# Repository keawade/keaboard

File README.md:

# keaboard

A split ergo 4x6 keyboard designed by Keith Wade.

Designed for use with the [nice!nano][nicenanoDocs] USB-C Bluetooth Pro Micro replacement
but also works with any Pro Micro compatible controllers like the Elite-C.

Inspired by the [ErgoTravel][ergotravel] keyboard designed by @jpconstantineau.

## Primary Features

- Split
- Columnular stagger
- Wireless option
- Hot swap MX switches
- Reversible PCB

## Revision 1

### PCB

### PCB Case

## Parts List

| Qty                   | Part                                                                                      |
| --------------------- | ----------------------------------------------------------------------------------------- |
| 2                     | Pro Micro footprint compatible microcontroller (Recommend Elite-C if not using nice!nano) |
| 50                    | MX compatible keyboard switches                                                           |  |
| 2 sets of 12 pins     | Mill-Max low profile sockets                                                              |
| 24 (get extra though) | Mill-Max low profile pins                                                                 |
| 50                    | Kailh MX hot swap sockets                                                                 |
| 50                    | MX compatible switches                                                                    |
| 50                    | [1N4148W SMD diodes][diodes]                                                              |
| 2                     | PJ-320A TRRS female jack  (not required if wireless with nice!nano)                       |
| 2                     | [EVQ-9P701P tactile switch](resetSwitch)                                                  |
| 24                    | M2 x 4 mm screws                                                                          |
| 12                    | M2 x 7mm stand offs                                                                       |

### Parts for Wireless Option

| Qty | Part                                                             |
| --- | ---------------------------------------------------------------- |
| 2   | [nice!nano][nicenanoStore]                                       |
| 2   | [CUS-12TB][slideSwitch] for power switch                         |
| 2   | 3.7v rechargeable battery                                        |
| 2   | [3-pin socket][batterySocket] (Can solder directly if preferred) |
| 2   | 2-pin plug                                                       |

## Firmware

- [QMK Firmware][keaboardQmk]
- [ZMK Firmware][keaboardZmk]

## Potential Future Revisions

- Choc hot swap
- RGB underglow
- LED backlight
- RGB backlight
- Design case for either 3D printing or CNC

[nicenanoDocs]: https://docs.nicekeyboards.com/#/nice!nano/
[nicenanoStore]: https://splitkb.com/collections/keyboard-parts/products/nice-nano-rev1-0
[ergotravel]: https://github.com/jpconstantineau/ErgoTravel
[batterySocket]: https://www.digikey.com/product-detail/en/DF3A-3P-2DS/H3894-ND/560460
[diodes]: https://www.digikey.com/product-detail/en/1N4148W-G+RHG/1N4148W-GRHGCT-ND/7644279
[slideSwitch]: https://www.digikey.com/product-detail/en/nidec-copal-electronics/CUS-12TB/563-1102-1-ND/1124231
[resetSwitch]: https://www.digikey.com/product-detail/en/panasonic-electronic-components/EVQ-9P701P/P19095CT-ND/5872974
[keaboardQmk]: https://github.com/keawade/qmk_firmware/tree/keaboard
[keaboardZmk]: https://github.com/keawade/keaboard-zmk-config

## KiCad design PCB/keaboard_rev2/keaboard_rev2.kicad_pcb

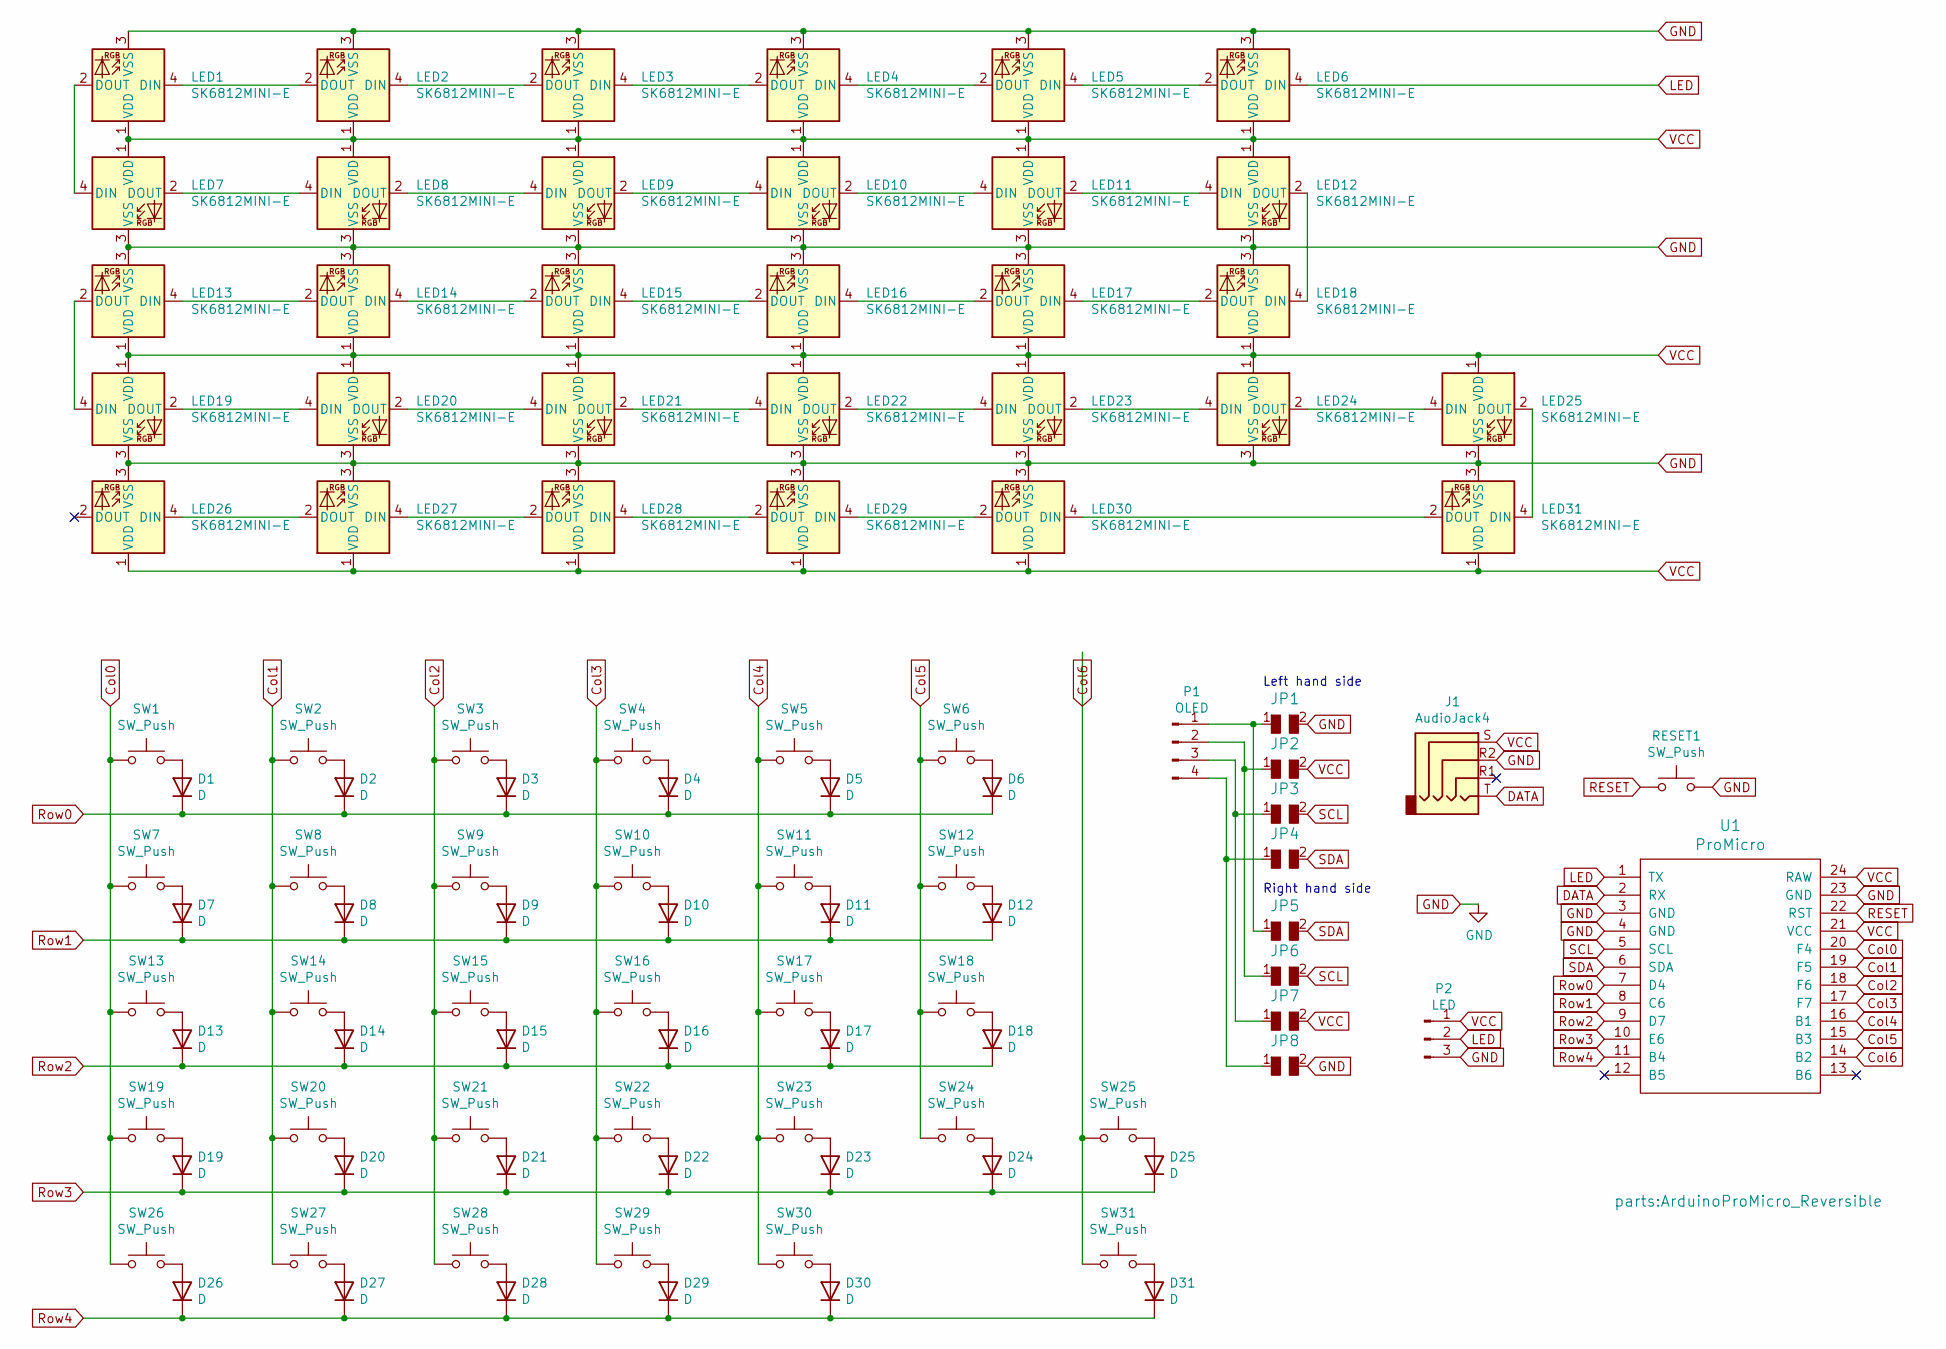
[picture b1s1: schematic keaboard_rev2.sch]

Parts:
D1, D2, D3, D4, D5, D6, D7, D8, D9, D10, D11, D12, D13, D14, D15, D16, D17, D18, D19, D20, D21, D22, D23, D24, D25, D26, D27, D28, D29, D30, D31: D; Diode-dual
J1: AudioJack4; TRRS-PJ-320A_reversible
JP1, JP8: GND; Jumper
JP2, JP7: VCC; Jumper
JP3, JP6: SCL; Jumper
JP4, JP5: SDA; Jumper
LED1, LED2, LED3, LED4, LED5, LED6, LED7, LED8, LED9, LED10, LED11, LED12, LED13, LED14, LED15, LED16, LED17, LED18, LED19, LED20, LED21, LED22, LED23, LED24, LED25, LED26, LED27, LED28, LED29, LED30, LED31: SK6812MINI-E; SK6812MINI-E_reversible
P1: OLED; OLED_v2
P2: LED; StripLED_reversible
RESET1: SW_Push; SW_EVQ-9P701P_reversible
SW1, SW2, SW3, SW4, SW5, SW6, SW7, SW8, SW9, SW10, SW11, SW12, SW13, SW14, SW15, SW16, SW17, SW18, SW19, SW20, SW21, SW22, SW23, SW24, SW25, SW26, SW27, SW28, SW29, SW30, SW31: SW_Push; Kailh_socket_PG1350_reversible
U1: ProMicro; ArduinoProMicro_Reversible

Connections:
Col0: SW1.1, SW7.1, SW13.1, SW19.1, SW26.1, U1.20 (F4)
Col1: SW2.1, SW8.1, SW14.1, SW20.1, SW27.1, U1.19 (F5)
Col2: SW3.1, SW9.1, SW15.1, SW21.1, SW28.1, U1.18 (F6)
Col3: SW4.1, SW10.1, SW16.1, SW22.1, SW29.1, U1.17 (F7)
Col4: SW5.1, SW11.1, SW17.1, SW23.1, SW30.1, U1.16 (B1)
Col5: SW6.1, SW12.1, SW18.1, SW24.1, U1.15 (B3)
Col6: SW25.1, SW31.1, U1.14 (B2)
DATA: J1.T, U1.2 (RX)
GND: J1.R2, JP1.2, JP8.2, LED1.3 (VSS), LED2.3 (VSS), LED3.3 (VSS), LED4.3 (VSS), LED5.3 (VSS), LED6.3 (VSS), LED7.3 (VSS), LED8.3 (VSS), LED9.3 (VSS), LED10.3 (VSS), LED11.3 (VSS), LED12.3 (VSS), LED13.3 (VSS), LED14.3 (VSS), LED15.3 (VSS), LED16.3 (VSS), LED17.3 (VSS), LED18.3 (VSS), LED19.3 (VSS), LED20.3 (VSS), LED21.3 (VSS), LED22.3 (VSS), LED23.3 (VSS), LED24.3 (VSS), LED25.3 (VSS), LED26.3 (VSS), LED27.3 (VSS), LED28.3 (VSS), LED29.3 (VSS), LED30.3 (VSS), LED31.3 (VSS), P2.3, RESET1.2, U1.3 (GND), U1.4 (GND), U1.23 (GND)
LED: LED6.4 (DIN), P2.2, U1.1 (TX)
unnamed: D1.2 (A), SW1.2
unnamed: D2.2 (A), SW2.2
unnamed: D3.2 (A), SW3.2
unnamed: D4.2 (A), SW4.2
unnamed: D5.2 (A), SW5.2
unnamed: D6.2 (A), SW6.2
unnamed: D7.2 (A), SW7.2
unnamed: D8.2 (A), SW8.2
unnamed: D9.2 (A), SW9.2
unnamed: D10.2 (A), SW10.2
unnamed: D11.2 (A), SW11.2
unnamed: D12.2 (A), SW12.2
unnamed: D13.2 (A), SW13.2
unnamed: D14.2 (A), SW14.2
unnamed: D15.2 (A), SW15.2
unnamed: D16.2 (A), SW16.2
unnamed: D17.2 (A), SW17.2
unnamed: D18.2 (A), SW18.2
unnamed: D19.2 (A), SW19.2
unnamed: D20.2 (A), SW20.2
unnamed: D21.2 (A), SW21.2
unnamed: D22.2 (A), SW22.2
unnamed: D23.2 (A), SW23.2
unnamed: D24.2 (A), SW24.2
unnamed: D25.2 (A), SW25.2
unnamed: D26.2 (A), SW26.2
unnamed: D27.2 (A), SW27.2
unnamed: D28.2 (A), SW28.2
unnamed: D29.2 (A), SW29.2
unnamed: D30.2 (A), SW30.2
unnamed: D31.2 (A), SW31.2
unnamed: JP1.1, JP5.1, P1.1
unnamed: JP2.1, JP6.1, P1.2
unnamed: JP3.1, JP7.1, P1.3
unnamed: JP4.1, JP8.1, P1.4
unnamed: LED1.2 (DOUT), LED7.4 (DIN)
unnamed: LED1.4 (DIN), LED2.2 (DOUT)
unnamed: LED2.4 (DIN), LED3.2 (DOUT)
unnamed: LED3.4 (DIN), LED4.2 (DOUT)
unnamed: LED4.4 (DIN), LED5.2 (DOUT)
unnamed: LED5.4 (DIN), LED6.2 (DOUT)
unnamed: LED7.2 (DOUT), LED8.4 (DIN)
unnamed: LED8.2 (DOUT), LED9.4 (DIN)
unnamed: LED10.2 (DOUT), LED11.4 (DIN)
unnamed: LED9.2 (DOUT), LED10.4 (DIN)
unnamed: LED11.2 (DOUT), LED12.4 (DIN)
unnamed: LED12.2 (DOUT), LED18.4 (DIN)
unnamed: LED13.2 (DOUT), LED19.4 (DIN)
unnamed: LED13.4 (DIN), LED14.2 (DOUT)
unnamed: LED14.4 (DIN), LED15.2 (DOUT)
unnamed: LED15.4 (DIN), LED16.2 (DOUT)
unnamed: LED16.4 (DIN), LED17.2 (DOUT)
unnamed: LED17.4 (DIN), LED18.2 (DOUT)
unnamed: LED19.2 (DOUT), LED20.4 (DIN)
unnamed: LED20.2 (DOUT), LED21.4 (DIN)
unnamed: LED21.2 (DOUT), LED22.4 (DIN)
unnamed: LED22.2 (DOUT), LED23.4 (DIN)
unnamed: LED23.2 (DOUT), LED24.4 (DIN)
unnamed: LED24.2 (DOUT), LED25.4 (DIN)
unnamed: LED25.2 (DOUT), LED31.4 (DIN)
unnamed: LED26.4 (DIN), LED27.2 (DOUT)
unnamed: LED27.4 (DIN), LED28.2 (DOUT)
unnamed: LED28.4 (DIN), LED29.2 (DOUT)
unnamed: LED29.4 (DIN), LED30.2 (DOUT)
unnamed: LED30.4 (DIN), LED31.2 (DOUT)
RESET: RESET1.1, U1.22 (RST)
Row0: D1.1 (K), D2.1 (K), D3.1 (K), D4.1 (K), D5.1 (K), D6.1 (K), U1.7 (D4)
Row1: D7.1 (K), D8.1 (K), D9.1 (K), D10.1 (K), D11.1 (K), D12.1 (K), U1.8 (C6)
Row2: D13.1 (K), D14.1 (K), D15.1 (K), D16.1 (K), D17.1 (K), D18.1 (K), U1.9 (D7)
Row3: D19.1 (K), D20.1 (K), D21.1 (K), D22.1 (K), D23.1 (K), D24.1 (K), D25.1 (K), U1.10 (E6)
Row4: D26.1 (K), D27.1 (K), D28.1 (K), D29.1 (K), D30.1 (K), D31.1 (K), U1.11 (B4)
SCL: JP3.2, JP6.2, U1.5 (SCL)
SDA: JP4.2, JP5.2, U1.6 (SDA)
VCC: J1.S, JP2.2, JP7.2, LED1.1 (VDD), LED2.1 (VDD), LED3.1 (VDD), LED4.1 (VDD), LED5.1 (VDD), LED6.1 (VDD), LED7.1 (VDD), LED8.1 (VDD), LED9.1 (VDD), LED10.1 (VDD), LED11.1 (VDD), LED12.1 (VDD), LED13.1 (VDD), LED14.1 (VDD), LED15.1 (VDD), LED16.1 (VDD), LED17.1 (VDD), LED18.1 (VDD), LED19.1 (VDD), LED20.1 (VDD), LED21.1 (VDD), LED22.1 (VDD), LED23.1 (VDD), LED24.1 (VDD), LED25.1 (VDD), LED26.1 (VDD), LED27.1 (VDD), LED28.1 (VDD), LED29.1 (VDD), LED30.1 (VDD), LED31.1 (VDD), P2.1, U1.21 (VCC), U1.24 (RAW)

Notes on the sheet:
Left hand side
Right hand side

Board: 2 copper layers, 106 parts (4 on the bottom side), 84 nets, no tracks yet.

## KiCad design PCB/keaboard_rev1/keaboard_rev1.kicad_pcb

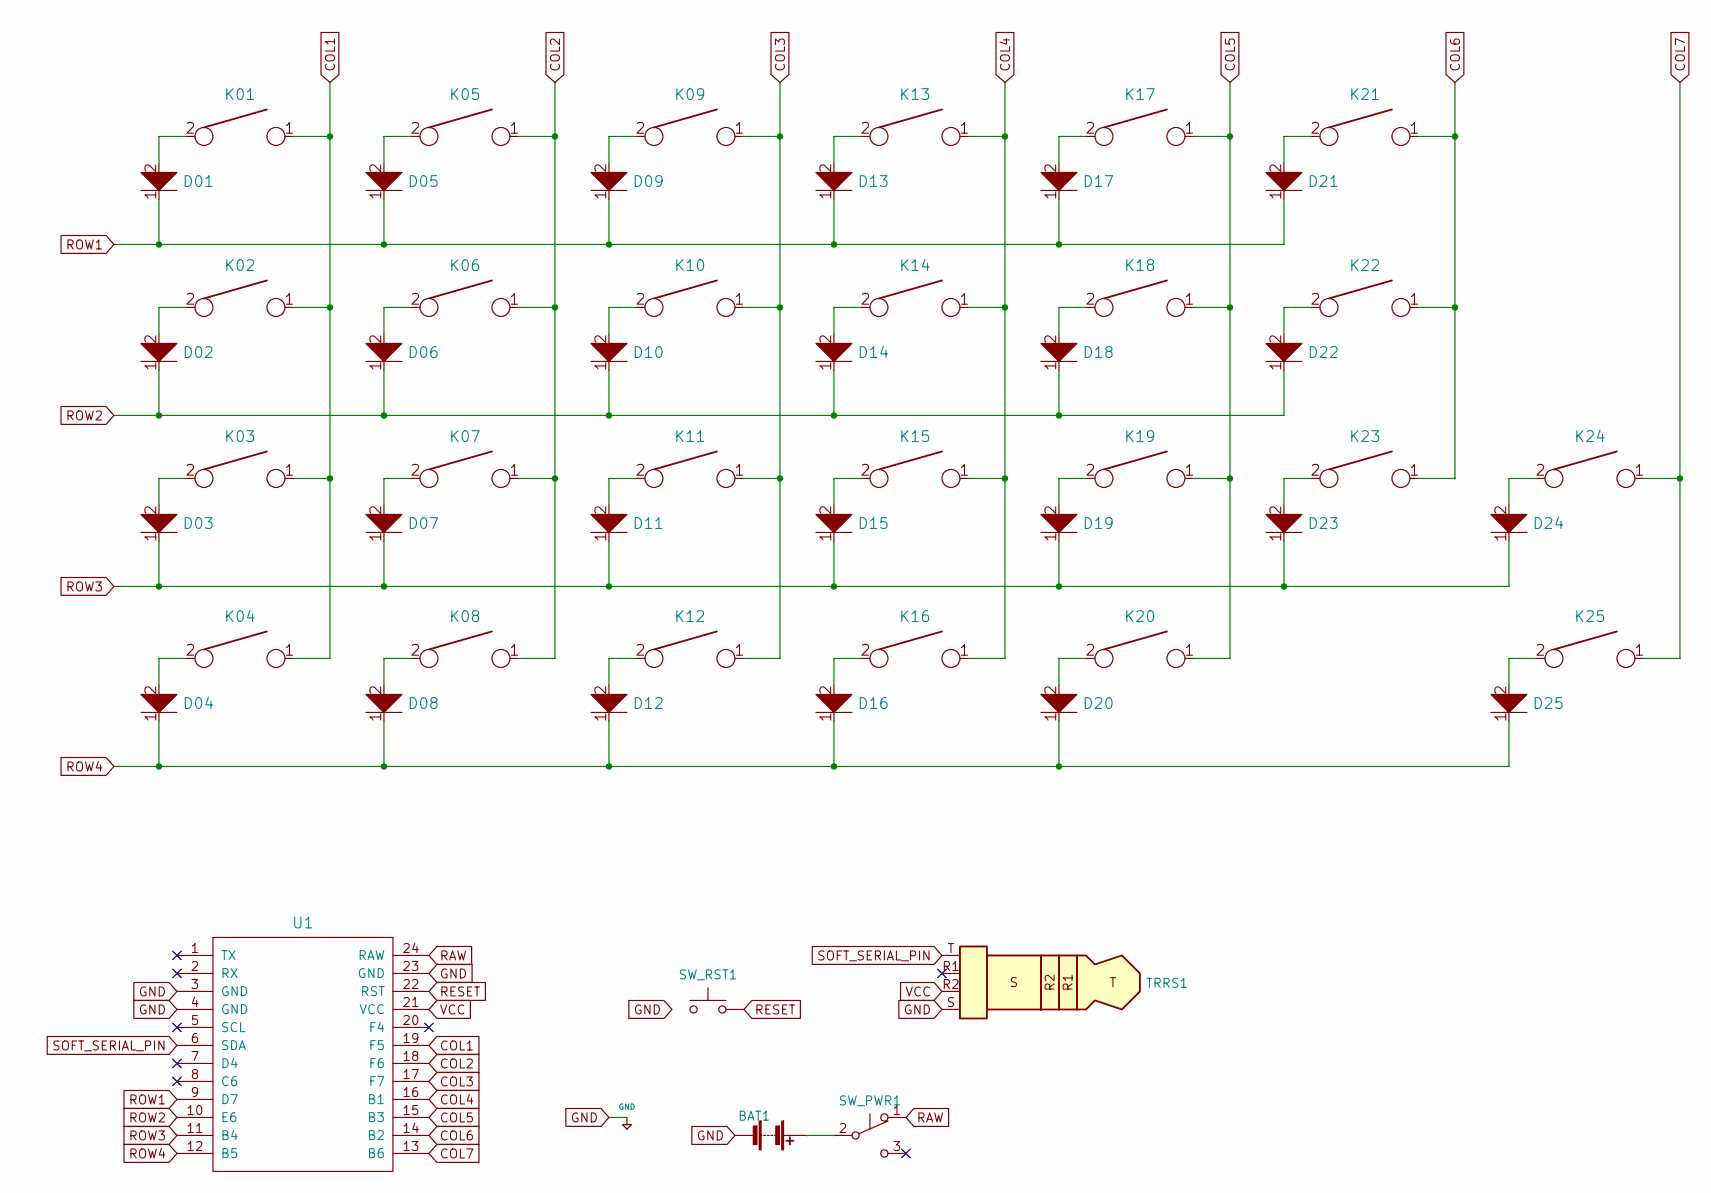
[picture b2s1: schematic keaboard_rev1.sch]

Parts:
BAT1: Battery; DF3A-3P-2DS_reversible
D01, D02, D03, D04, D05, D06, D07, D08, D09, D10, D11, D12, D13, D14, D15, D16, D17, D18, D19, D20, D21, D22, D23, D24, D25: D; D_SOD123_reversible
K01, K02, K03, K04, K05, K06, K07, K08, K09, K10, K11, K12, K13, K14, K15, K16, K17, K18, K19, K20, K21, K22, K23, K24, K25: KEYSW; Kailh_socket_MX_reversible
SW_PWR1: SW_Push_SPDT; SW_PCM12SMTR_reversible
SW_RST1: SW_EVQ-9P701P; SW_EVQ-9P701P_reversible
TRRS1: TRRS Jack; TRRS-PJ-320A_reversible
U1: ProMicro; ArduinoProMicro_Reversible

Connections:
COL1: K01.1, K02.1, K03.1, K04.1, U1.19 (F5)
COL2: K05.1, K06.1, K07.1, K08.1, U1.18 (F6)
COL3: K09.1, K10.1, K11.1, K12.1, U1.17 (F7)
COL4: K13.1, K14.1, K15.1, K16.1, U1.16 (B1)
COL5: K17.1, K18.1, K19.1, K20.1, U1.15 (B3)
COL6: K21.1, K22.1, K23.1, U1.14 (B2)
COL7: K24.1, K25.1, U1.13 (B6)
GND: BAT1.2 (-), SW_RST1.1 (A), SW_RST1.2 (A), TRRS1.S, U1.3 (GND), U1.4 (GND), U1.23 (GND)
unnamed: BAT1.1 (+), SW_PWR1.2 (B)
unnamed: D01.2, K01.2
unnamed: D02.2, K02.2
unnamed: D03.2, K03.2
unnamed: D04.2, K04.2
unnamed: D05.2, K05.2
unnamed: D06.2, K06.2
unnamed: D07.2, K07.2
unnamed: D08.2, K08.2
unnamed: D09.2, K09.2
unnamed: D10.2, K10.2
unnamed: D11.2, K11.2
unnamed: D12.2, K12.2
unnamed: D13.2, K13.2
unnamed: D14.2, K14.2
unnamed: D15.2, K15.2
unnamed: D16.2, K16.2
unnamed: D17.2, K17.2
unnamed: D18.2, K18.2
unnamed: D19.2, K19.2
unnamed: D20.2, K20.2
unnamed: D21.2, K21.2
unnamed: D22.2, K22.2
unnamed: D23.2, K23.2
unnamed: D24.2, K24.2
unnamed: D25.2, K25.2
RAW: SW_PWR1.1 (A), U1.24 (RAW)
RESET: SW_RST1.3 (B), SW_RST1.4 (B), U1.22 (RST)
ROW1: D01.1, D05.1, D09.1, D13.1, D17.1, D21.1, U1.9 (D7)
ROW2: D02.1, D06.1, D10.1, D14.1, D18.1, D22.1, U1.10 (E6)
ROW3: D03.1, D07.1, D11.1, D15.1, D19.1, D23.1, D24.1, U1.11 (B4)
ROW4: D04.1, D08.1, D12.1, D16.1, D20.1, D25.1, U1.12 (B5)
SOFT_SERIAL_PIN: TRRS1.T, U1.6 (SDA)
VCC: TRRS1.R2, U1.21 (VCC)

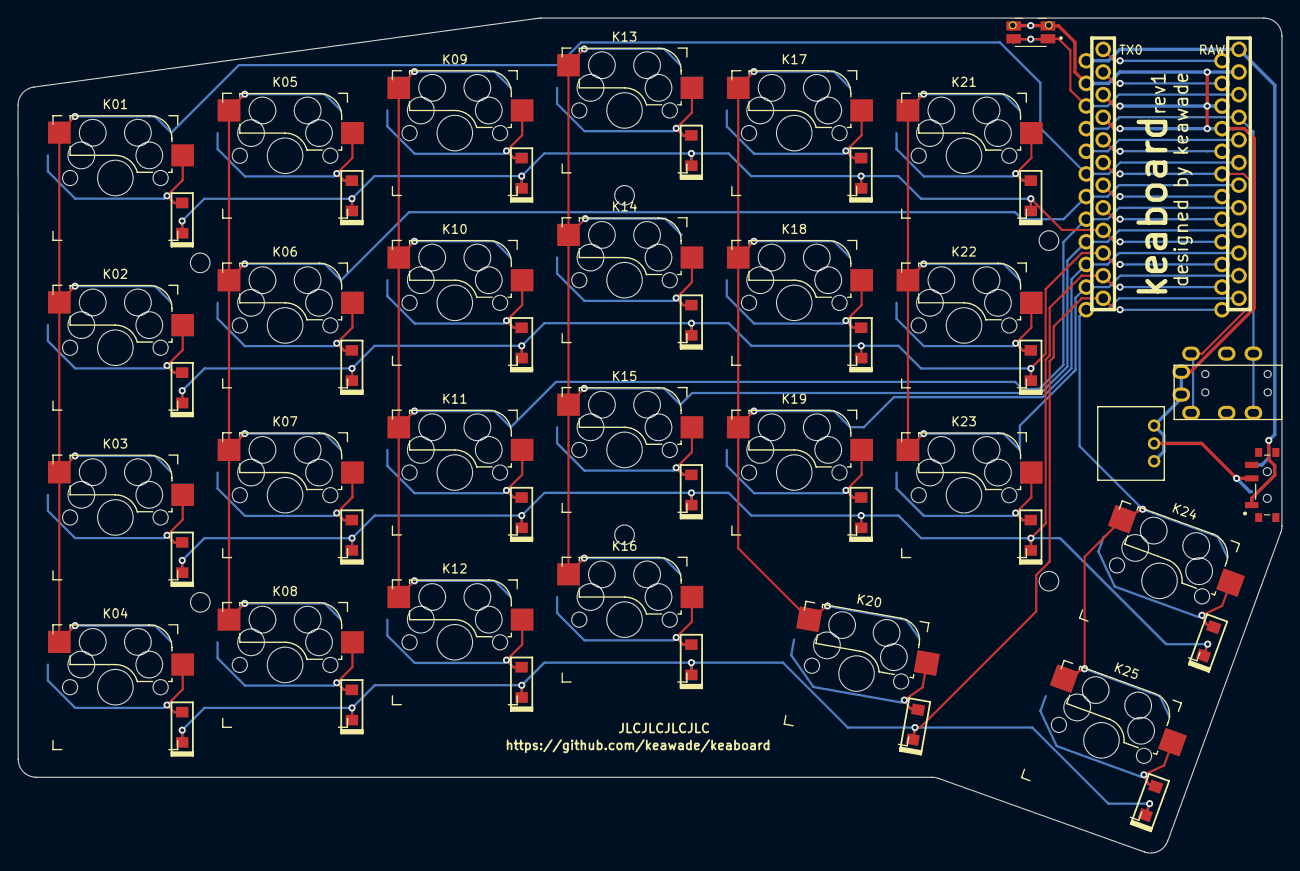
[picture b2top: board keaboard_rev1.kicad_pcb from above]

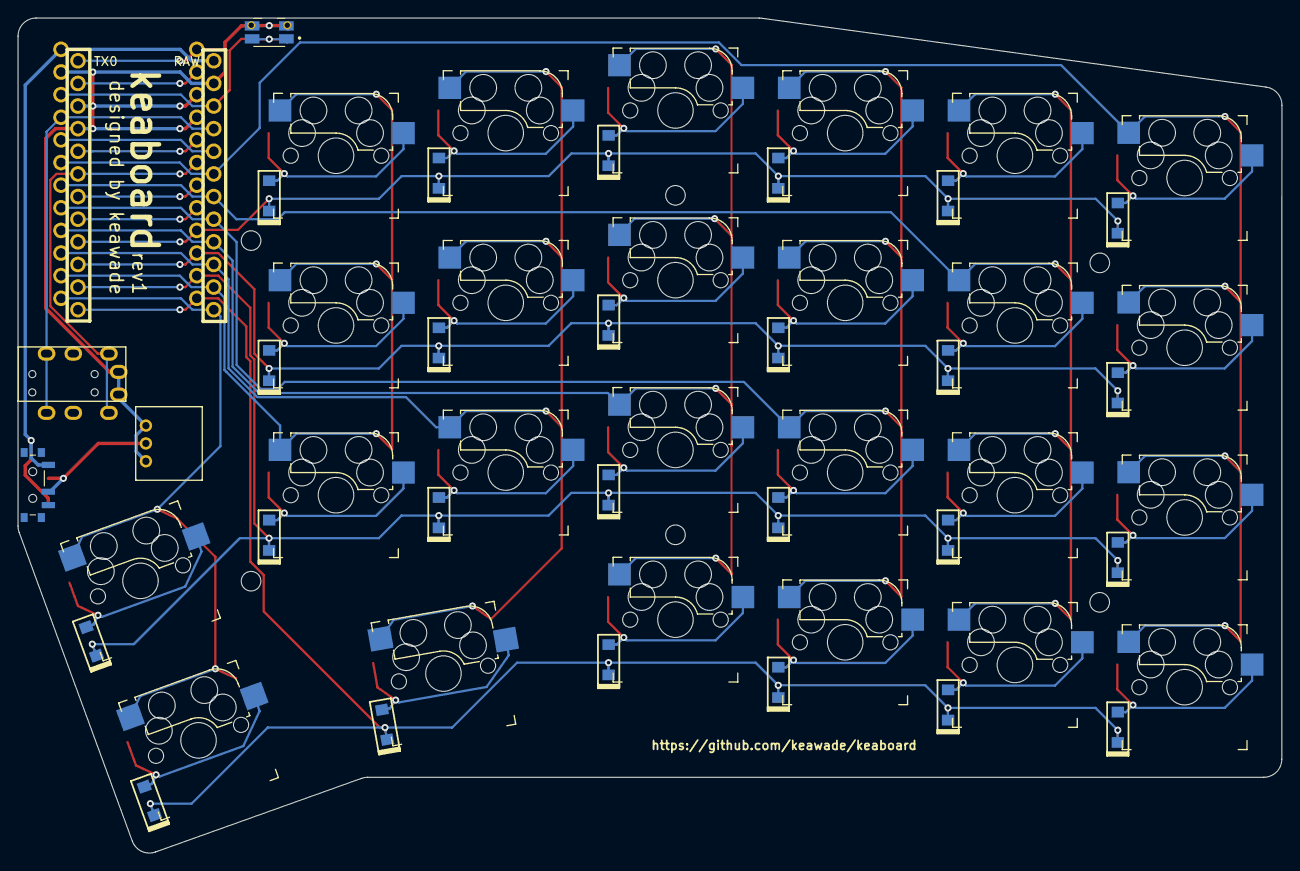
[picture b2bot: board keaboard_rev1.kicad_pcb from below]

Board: 2 copper layers, 141.9 x 93.7 mm, 55 parts (25 on the bottom side), 42 nets.

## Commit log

2020-06-19 Initialize KiCad project
2020-06-19 Add recommended keyboard libraries
2020-08-18 Flip sockets to correct side, adjust diode placement, place controller
2020-08-18 Add readme
2020-08-18 Remove old kicad files
2020-08-18 Actually commit the source files
    Yikes EasyEDA is kind of a mess
2020-08-18 Add render
2020-08-19 Clean up dir
2020-08-19 Create KiCAD project
2020-08-20 Switch layout, diodes
2020-08-20 Add traces, add TRRS jack, add B+/B- pins, update README
2020-08-20 Update WIP screenshot
2020-08-20 Update TODOs
2020-08-21 Connect matrix to data pins
2020-08-21 Minor rerouting, add reset switch, add edge cut
2020-08-21 Add keaboard label
2020-08-21 Update readme with TODOs from feedback
2020-08-22 Add partslist
2020-08-22 Add 3-pin JST connector, remove B+/B- pin holes
2020-08-22 Clean up kicad mod directories
2020-08-22 Reroute TRRS connection, reroute row connections, move progress images
2020-08-22 Remove old files
2020-08-22 Core reversible PCB designs
2020-08-22 Keyboard layout and cutout
2020-08-23 Add reset switch, add power switch, add docs
2020-08-23 Update image references
2020-08-23 Route traces for matrix
2020-08-23 Add label, update README
2020-08-23 Remove outdated notes
2020-08-23 WIP, created WIP reversible footprints, created schematic, updated board with schematic
2020-08-23 Footprints laid out from schematic
2020-08-23 Wired matrix
2020-08-23 Fix reset switch, wire reset switch, wire grounds
2020-08-23 Update images
2020-08-23 Connect battery, fix unconnected lines
2020-08-23 Place label
2020-08-23 Move battery plug
2020-08-23 PDF schematic, add screw holes, update README
2020-08-23 Add labels to battery plug, update battery plug footprint to correctly map pin holes, reroute traces to battery plug
2020-08-23 Update image
2020-08-23 Add 'on >' label on back the board relative to the switch
2020-08-23 Put DF3 plug back in links
2020-08-23 Update pcb image, generate gerber
2020-08-23 Zip gerber
2020-08-23 Case top plate
2020-08-23 TopPlate and BottomPlate
2020-08-23 Generate and zip gerber for plates
2020-08-25 Add pcb render to readme
2020-08-25 Resize PCB to add more space around the edges to avoid breaking parts, update images, update gerber
2020-08-25 Organize images, add top/bottom plate renders
2020-09-01 Update schematic, update footprints, start updating layout
2020-09-02 Update cases, update edge cuts on main pcb, start routing traces to controller
2020-09-02 Route traces, add labels
2020-09-02 Update gerber
2020-09-02 Remove switch numbering from top plate
2020-09-02 Update README images
2020-09-02 Fix missing trace
2020-09-08 Update schematic, TODO: Update pcb
2020-09-09 Update PCB to fix incorrect trace
2020-09-09 Update images and readme
2020-09-12 Improve labeling
2020-09-18 Initialize rev2 kicad project
2020-09-23 RGB led WIP
2020-09-23 Update to image of final board
2020-09-23 Update parts list
2020-09-23 Add links to firmware, misc tweaks
2021-04-30 WIP rev2
    Just traces remaining
2021-04-30 Update super outdated rev1 pdf
2021-04-30 Fix schematic/net mistake from old rev1 pdf
2021-04-30 Export DSN
2021-04-30 Add keep out areas
2021-04-30 Set up net classes
2021-04-30 Generate DSN
2021-05-01 Fix issue where kicad could not determine board outline
2021-05-01 Reorder LEDs in schematic for better routing
2021-05-02 Better footprints, OLED, misc
